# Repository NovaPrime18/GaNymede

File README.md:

# GaNymede

**Open 60 V, 100 A peak three-phase GaN motor controller, VESC compatible.**

<table><tr>
<td></td>
<td></td>
</tr></table>

---

## Overview

GaNymede is an open-source, 60 V three-phase motor controller built around six EPC2361 eGaN FETs and three LMG1210 half-bridge drivers. It is sized for a direct-drive hub motor: **50 A phase current continuously, 100 A phase peak for one minute**, with phase-current and phase-voltage sensing on every leg, Hall inputs, and an ESP32-C3 for wireless telemetry.

The board is a compact 78 × 65 mm six-layer design, with the bus capacitor bank wrapped around the power stage and the copper pours sized around the full 100 A phase peak. The control side follows the familiar VESC pattern — STM32F405, three Hall inputs, three phase-current channels.

This repository is the hardware design; it does not include firmware.

LLMs were used in the design of this driver, specifically Deepseek-V4.1-Flash(1017) was used to do schematic reviews, loss analysis, component finding.

---

## Specifications

| Parameter | Value |
|---|---|
| Bus voltage | up to 60 V DC |
| Phase current | 50 A continuous · 100 A peak (1 min) |
| Peak output power | ≈ 5.2 kW at 100 A phase peak (m = 1, modelled) |
| Topology | 3-phase inverter, 6× EPC2361 100 V eGaN |
| Switching frequency | 20 kHz nominal design point (10–40 kHz analysed) |
| Gate drive | LMG1210, 5 V, 2.2 Ω |
| Current sense | 0.25 mΩ per phase, INA240A1 |
| Control | STM32F405RGT6, 168 MHz, 8 MHz HSE |
| Wireless | ESP32-C3-WROOM-02 (Wi-Fi / BLE) |
| CAN | 2× TJA1051TK-3 (STM32 + ESP32), shared bus |
| Input | XT90 |
| Phase outputs | 3× 3 mm plated through-holes (U / V / W) |
| PCB | 78 × 65 mm, 6-layer, 1.6 mm, 1 oz Cu |

Phase currents are amplitudes, not RMS: 100 A peak is 70.7 A RMS.

---

## Hardware

| Component | Part |
|---|---|
| MCU | STM32F405RGT6 (LQFP-64) |
| Wireless | ESP32-C3-WROOM-02 |
| Power stage FETs | 6× EPC2361 (100 V eGaN) |
| Gate drivers | 3× LMG1210 |
| Current sense | 3× INA240A1, 0.25 mΩ per phase |
| Input connector | XT90 |
| Phase outputs | 3× 3 mm plated through-holes |

### Power stage

- Six EPC2361 100 V eGaN FETs, two per phase, switching a 60 V bus. The 100 V rating leaves headroom for turn-off overshoot; the real margin depends on power-loop inductance and is worth a double-pulse check.
- Each phase uses an LMG1210 driven from 5 V with 2.2 Ω gate resistors. DHL and DLH are strapped high, selecting independent high/low inputs — **dead time is set in firmware**, not by the driver.
- Bootstrap diodes are BAT46WS; each phase carries a 2.2 nF + 1 Ω snubber.
- Phase current is measured across 2× 0.5 mΩ 2512 resistors in parallel (0.25 mΩ per phase) into an INA240A1 at a gain of 20.
- The bus capacitor bank is roughly 1.4 mF (8× 100 µF 80 V, 12× 47 µF 100 V, plus ceramics), protected by an SMAJ60A TVS.
- Phase outputs land on three 3 mm plated through-holes labelled U, V and W.

---

## Thermal & loss budget

[`LOSSES.md`](LOSSES.md) contains the full copper, semiconductor and thermal model. These are **modelled** numbers, not measurements:

| | 100 A peak (1 min) | 50 A continuous |
|---|---|---|
| Total loss | ≈ 29 W | ≈ 7.3 W |
| Efficiency | ≈ 99.4 % | ≈ 99.7 % |
| Junction temperature | 45 → 62 °C | 43 °C |

Assumptions: 60 V bus, 20 kHz switching, 0.25 mΩ shunts, 0.4 mm / 6 W/mK thermal pads, 30 °C ambient — the addendum case in `LOSSES.md`.

- The **phase shunts and the 60 V / GND copper** dominate the loss budget, not the six GaNs.
- The heatsink needs to handle roughly 5–6 W continuous and up to ~20 W by the end of a 100 A minute. A 1.5–2 °C/W natural-convection sink is enough, or bolt the plate to the frame.
- The thermal pad matters more than the heatsink: a flat, thin, high-conductivity pad is worth tens of degrees at 100 A.
- The one-minute 100 A rating is limited by thermal mass, not by the heatsink.

---

## Acknowledgements / Based On

- [**VESC / bldc**](https://github.com/vedderb/bldc) — the open BLDC controller ecosystem and the control-side conventions this board follows.
- [**nitride-nano**](https://github.com/NovaPrime18/nitride-nano) — README layout, and the copper-loss analysis method reused in `LOSSES.md`.

---

## License

Hardware design files are licensed under the **CERN Open Hardware Licence Version 2 – Strongly Reciprocal (CERN-OHL-S v2.0)**.

See [`LICENSE`](./LICENSE) for the full text, or visit [ohwr.org/cern_ohl_s_v2](https://ohwr.org/cern_ohl_s_v2.txt).

> In short: you are free to use, study, modify, and distribute this design, provided that any derivatives are released under the same licence and source files are made available.

---

## Status

> 🚧 Work in progress — schematic and 6-layer layout are drawn; The current and thermal figures above are design targets from the loss model, not measured ratings.

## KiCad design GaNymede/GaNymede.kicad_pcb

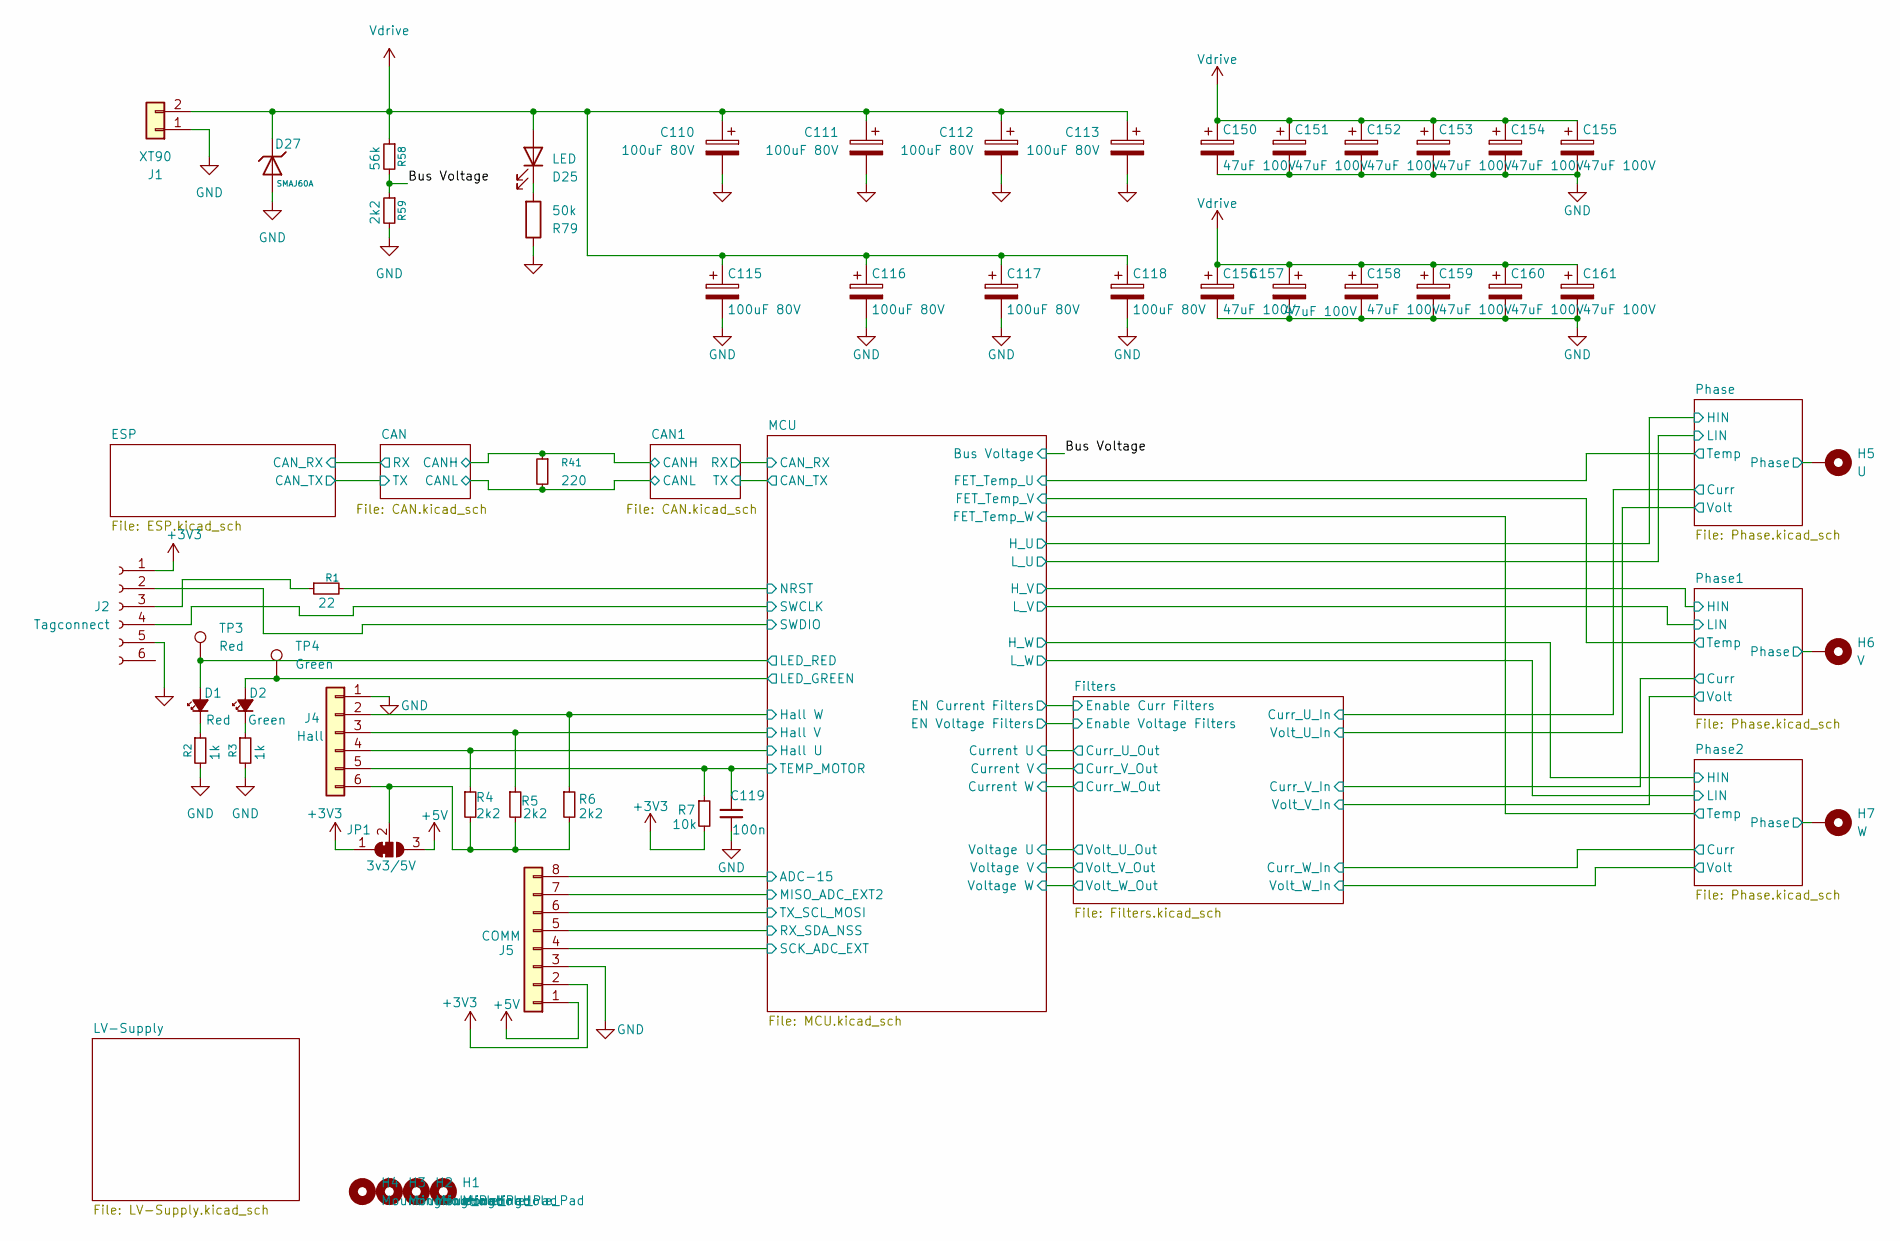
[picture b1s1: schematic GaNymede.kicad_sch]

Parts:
C110, C111, C112, C113, C115, C116, C117, C118: 100uF 80V; CP_Elec_10x10; LCSC C487410
C119: 100n; C_0402_1005Metric
C150, C151, C152, C153, C154, C155, C156, C157, C158, C159, C160, C161: 47uF 100V; CP_Elec_8x10; MPN RV100V47M8X10; LCSC C48935391
D1: Red; LED_0603_1608Metric; LCSC C2286
D2: Green; LED_0603_1608Metric; LCSC C84267
D25: LED; LED_0603_1608Metric; LCSC C2286
D27: SMAJ60A; D_SMA; Part SMAJ60A; LCSC C42394398
H1, H2, H3, H4: MountingHole_Pad; MountingHole_2.7mm_M2.5
H5: U; MountingHole_3mm_Pad_Via
H6: V; MountingHole_3mm_Pad_Via
H7: W; MountingHole_3mm_Pad_Via
J1: XT90; TH_XT90PB-M; JLC C3040688
J2: Tagconnect; Tag-Connect_TC2030-IDC-NL_2x03_P1.27mm_Vertical
J4: Hall; JST_PH_B6B-PH-SM4-TB_1x06-1MP_P2.00mm_Vertical; LCSC C471518
J5: COMM; JST_PH_B8B-PH-SM4-TB_1x08-1MP_P2.00mm_Vertical; LCSC C495548
JP1: 3v3/5V; SolderJumper-3_P1.3mm_Bridged12_RoundedPad1.0x1.5mm
R1: 22; R_0402_1005Metric; LCSC C25092
R2, R3: 1k; R_0402_1005Metric; LCSC C11702
R4, R5, R6: 2k2; R_0402_1005Metric
R7: 10k; R_0402_1005Metric
R41: 220; R_0603_1608Metric; LCSC C22962
R58: 56k; R_0603_1608Metric; LCSC C23206
R59: 2k2; R_0402_1005Metric; LCSC C25879
R79: 50k; R_0402_1005Metric; LCSC C25897
TP3: Red; TestPoint_Pad_D1.5mm
TP4: Green; TestPoint_Pad_D1.5mm

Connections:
+3V3: J2.1, J5.2, JP1.1 (A), R7.2; also elsewhere on the board
+5V: J5.1, JP1.3 (B); also elsewhere on the board
/Bus Voltage: R58.2, R59.1; also elsewhere on the board
/CAN/CANH: R41.1; also elsewhere on the board
/CAN/CANL: R41.2; also elsewhere on the board
/MCU/ADC-15: J5.8; also elsewhere on the board
/MCU/Hall U: J4.4, R4.1; also elsewhere on the board
/MCU/Hall V: J4.3, R5.1; also elsewhere on the board
/MCU/Hall W: J4.2, R6.1; also elsewhere on the board
/MCU/LED_GREEN: D2.2 (A), TP4.1 (1_1); also elsewhere on the board
/MCU/LED_RED: D1.2 (A), TP3.1 (1_1); also elsewhere on the board
/MCU/MISO_ADC_EXT2: J5.7; also elsewhere on the board
/MCU/NRST: R1.2; also elsewhere on the board
/MCU/RX_SDA_NSS: J5.5; also elsewhere on the board
/MCU/SCK_ADC_EXT: J5.4; also elsewhere on the board
/MCU/SWCLK: J2.4; also elsewhere on the board
/MCU/SWDIO: J2.2; also elsewhere on the board
/MCU/TEMP_MOTOR: C119.1, J4.5, R7.1; also elsewhere on the board
/MCU/TX_SCL_MOSI: J5.6; also elsewhere on the board
/Phase1/Phase: H6.1 (1_1); also elsewhere on the board
/Phase2/Phase: H7.1 (1_1); also elsewhere on the board
/Phase/Phase: H5.1 (1_1); also elsewhere on the board
GND: C110.2, C111.2, C112.2, C113.2, C115.2, C116.2, C117.2, C118.2, C119.2, C150.2, C151.2, C152.2, C153.2, C154.2, C155.2, C156.2, C157.2, C158.2, C159.2, C160.2, C161.2, D27.2, J1.1, J2.5, J4.1, J5.3, R2.2, R3.2, R59.2, R79.1; also elsewhere on the board
unnamed: D1.1 (K), R2.1
unnamed: D2.1 (K), R3.1
unnamed: D25.1 (K), R79.2
unnamed: J2.3, R1.1
unnamed: J4.6, JP1.2 (C), R4.2, R5.2, R6.2
Vdrive: C110.1, C111.1, C112.1, C113.1, C115.1, C116.1, C117.1, C118.1, C150.1, C151.1, C152.1, C153.1, C154.1, C155.1, C156.1, C157.1, C158.1, C159.1, C160.1, C161.1, D25.2 (A), D27.1, J1.2, R58.1; also elsewhere on the board

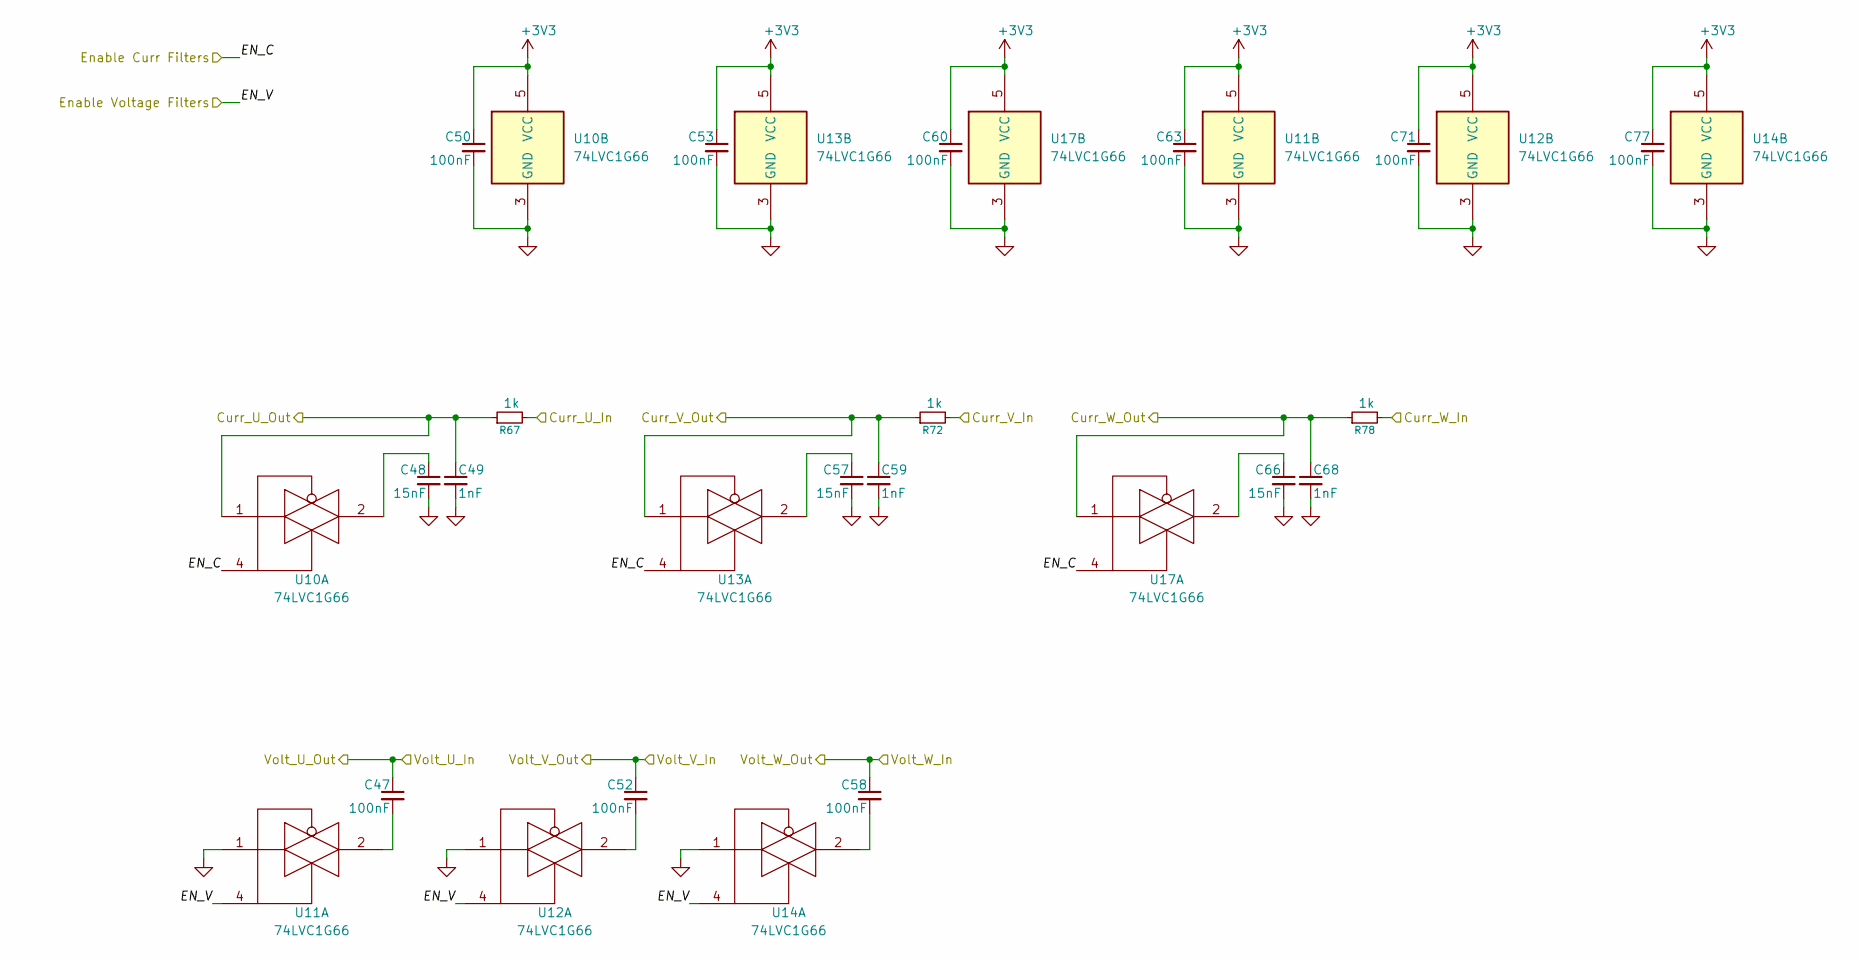
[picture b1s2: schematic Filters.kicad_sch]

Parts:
C47, C50, C52, C53, C58, C60, C63, C71, C77: 100nF; C_0402_1005Metric; LCSC C307331
C48, C57, C66: 15nF; C_0402_1005Metric; LCSC C114405
C49, C59, C68: 1nF; C_0402_1005Metric; LCSC C1523
R67, R72, R78: 1k; R_0402_1005Metric; LCSC C11702
U10, U11, U12, U13, U14, U17: 74LVC1G66; SOT-353_SC-70-5; JLC C97489

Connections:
+3V3: C50.1, C53.1, C60.1, C63.1, C71.1, C77.1, U10.5 (VCC), U11.5 (VCC), U12.5 (VCC), U13.5 (VCC), U14.5 (VCC), U17.5 (VCC); also elsewhere on the board
/Filters/Curr_U_In: R67.2; also elsewhere on the board
/Filters/Curr_U_Out: C49.1, R67.1, U10.1; also elsewhere on the board
/Filters/Curr_V_In: R72.2; also elsewhere on the board
/Filters/Curr_V_Out: C59.1, R72.1, U13.1; also elsewhere on the board
/Filters/Curr_W_In: R78.2; also elsewhere on the board
/Filters/Curr_W_Out: C68.1, R78.1, U17.1; also elsewhere on the board
/Filters/EN_C: U10.4, U13.4, U17.4; also elsewhere on the board
/Filters/EN_V: U11.4, U12.4, U14.4; also elsewhere on the board
/Filters/Volt_U_In: C47.1; also elsewhere on the board
/Filters/Volt_V_In: C52.1; also elsewhere on the board
/Filters/Volt_W_In: C58.1; also elsewhere on the board
GND: C48.2, C49.2, C50.2, C53.2, C57.2, C59.2, C60.2, C63.2, C66.2, C68.2, C71.2, C77.2, U10.3 (GND), U11.1, U11.3 (GND), U12.1, U12.3 (GND), U13.3 (GND), U14.1, U14.3 (GND), U17.3 (GND); also elsewhere on the board
unnamed: C47.2, U11.2
unnamed: C48.1, U10.2
unnamed: C52.2, U12.2
unnamed: C57.1, U13.2
unnamed: C58.2, U14.2
unnamed: C66.1, U17.2

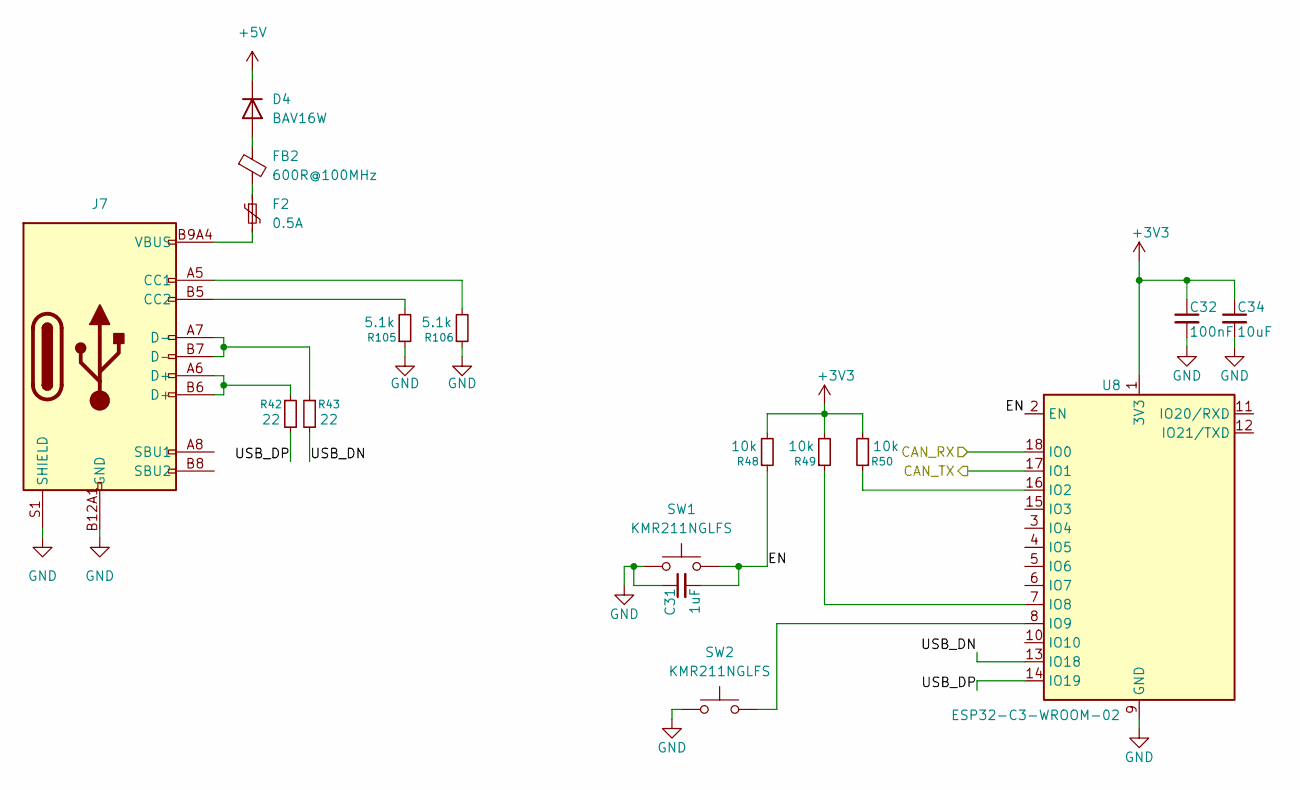
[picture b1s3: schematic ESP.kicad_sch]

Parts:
C31: 1uF; C_0402_1005Metric; LCSC C52923
C32: 100nF; C_0402_1005Metric; LCSC C307331
C34: 10uF; C_0805_2012Metric; LCSC C440198
D4: BAV16W; D_SOD-123; JLC C459527
F2: 0.5A; R_0805_2012Metric; JLC C2833485
FB2: 600R@100MHz; L_0402_1005Metric; LCSC C76884
J7: Connector, USB-TYPE-C-16P; TYPE-C-SMD_HX-TYPE-C-16PIN; LCSC C2927039
R42, R43: 22; R_0402_1005Metric; LCSC C25092
R48, R49, R50: 10k; R_0402_1005Metric; LCSC C25744
R105, R106: 5.1k; R_0402_1005Metric; LCSC C25905
SW1, SW2: KMR211NGLFS; SW_Push_1P1T_NO_CK_KMR2; JLC C221676
U8: ESP32-C3-WROOM-02; JLC C2934560

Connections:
+3V3: C32.1, C34.1, R48.2, R49.2, R50.2, U8.1 (3V3); also elsewhere on the board
+5V: D4.1 (K); also elsewhere on the board
/CAN/RX: U8.18 (IO0); also elsewhere on the board
/CAN/TX: U8.17 (IO1); also elsewhere on the board
/ESP/EN: C31.2, R48.1, SW1.2, U8.2 (EN)
/ESP/USB_DN: R43.2, U8.13 (IO18)
/ESP/USB_DP: R42.2, U8.14 (IO19)
GND: C31.1, C32.2, C34.2, J7.A12B1 (GND), J7.B12A1 (GND), J7.S1 (SHIELD), R105.1, R106.1, SW1.1, SW2.1, U8.9 (GND), U8.19 (GND); also elsewhere on the board
unnamed: D4.2 (A), FB2.1
unnamed: F2.1, FB2.2
unnamed: F2.2, J7.A9B4 (VBUS), J7.B9A4 (VBUS)
unnamed: J7.A5 (CC1), R106.2
unnamed: J7.B5 (CC2), R105.2
unnamed: J7.A6 (D+), J7.B6 (D+), R42.1
unnamed: J7.A7 (D-), J7.B7 (D-), R43.1
unnamed: R50.1, U8.16 (IO2)
unnamed: R49.1, U8.7 (IO8)
unnamed: SW2.2, U8.8 (IO9)

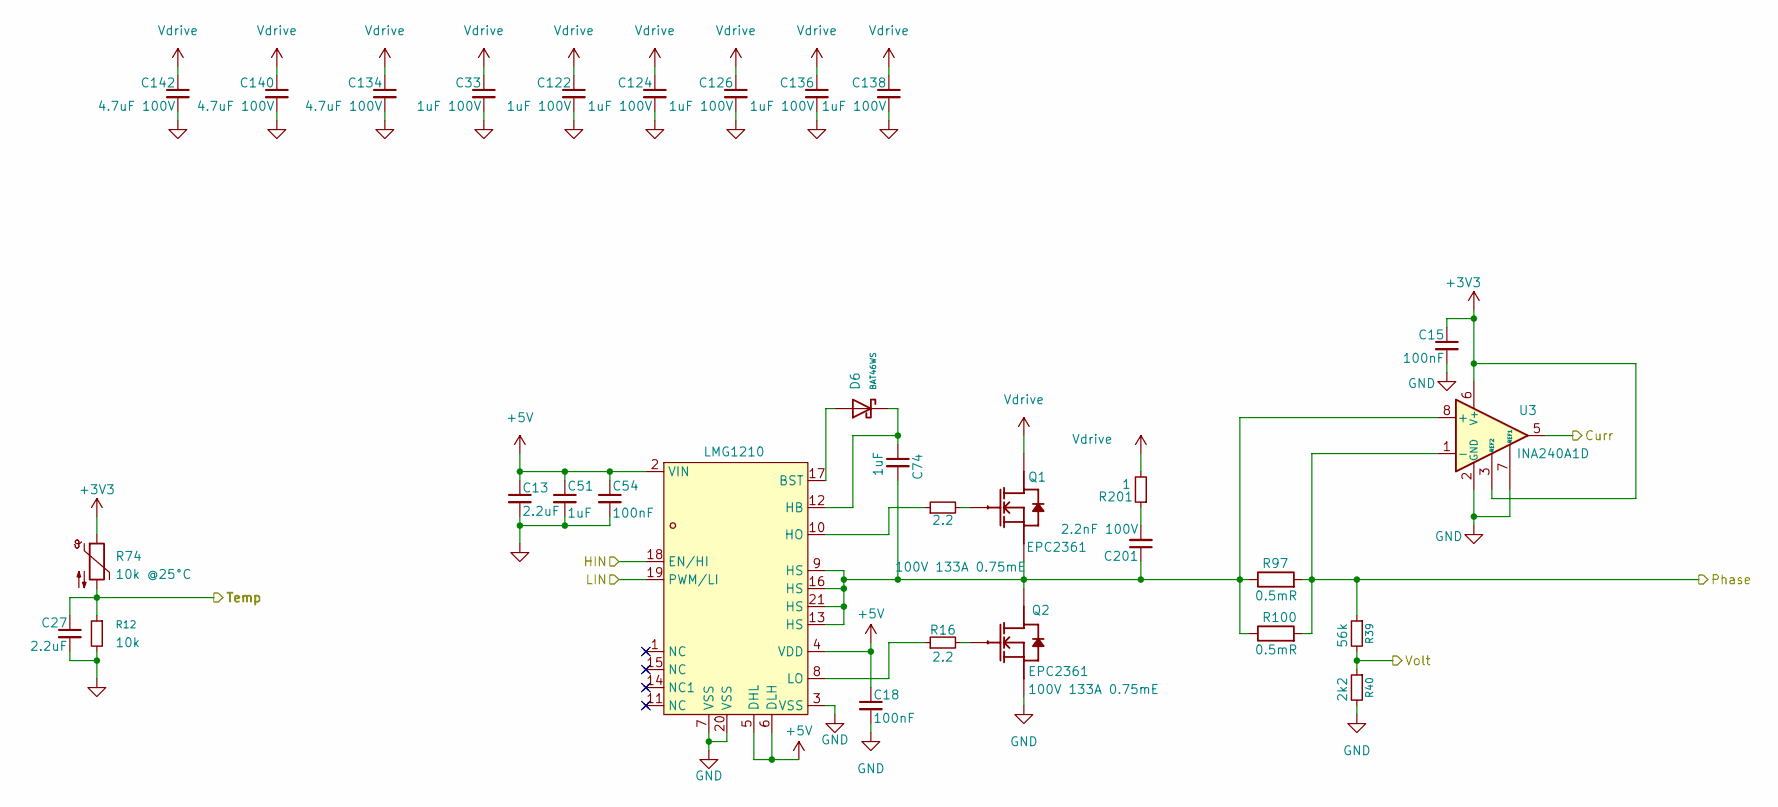
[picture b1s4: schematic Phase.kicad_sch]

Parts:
C13, C27: 2.2uF; C_0402_1005Metric; LCSC C20539421
C15, C18: 100nF; C_0402_1005Metric; LCSC C307331
C33, C122, C124, C126, C136, C138: 1uF 100V; C_0805_2012Metric; LCSC C5370002
C51, C74: 1uF; C_0402_1005Metric
C54: 100nF; C_0402_1005Metric
C134, C140, C142: 4.7uF 100V; C_1206_3216Metric; LCSC C22367839
C201: 2.2nF 100V; C_0805_2012Metric; MPN CC0805KRX7R0BB222; LCSC C107136
D6: BAT46WS; D_SOD-323; Forward Voltage (Vf@If) 1V@250mA; Reverse Voltage (Vr) 100V; Part BAT46WS; LCSC C7502692
Q1, Q2: EPC2361; D0606F_100V
R12: 10k; R_0402_1005Metric; LCSC C25744
R13, R16: 2.2; R_0402_1005Metric
R39: 56k; R_0603_1608Metric; LCSC C23206
R40: 2k2; R_0402_1005Metric; LCSC C25879
R74: 10k @25°C; R_0402_1005Metric; LCSC C77131
R97, R100: 0.5mR; R_2512_6332Metric
R201: 1; R_1210_3225Metric; MPN FRC1210J1R0 TS; LCSC C2974068
U3: INA240A1D; SOIC-8_3.9x4.9mm_P1.27mm; LCSC C1346458
U19: LMG1210; WQFN-19_L4.0-W3.0-P0.50-BL-EP_LMG1210RVRR; MPN LMG1210RVRR; LCSC Part C2677136

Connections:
+3V3: C15.1, R74.1, U3.3 (REF2), U3.6 (V+); also elsewhere on the board
+5V: C13.1, C18.1, C51.1, C54.1, U19.2 (VIN), U19.4 (VDD), U19.5 (DHL), U19.6 (DLH); also elsewhere on the board
/Filters/Curr_U_In: U3.5; also elsewhere on the board
/Filters/Volt_U_In: R39.2, R40.1; also elsewhere on the board
/MCU/FET_Temp_U: C27.1, R12.1, R74.2; also elsewhere on the board
/MCU/H_U: U19.18 (EN/HI); also elsewhere on the board
/MCU/L_U: U19.19 (PWM/LI); also elsewhere on the board
/Phase/Phase: R39.1, R97.2, R100.2, U3.1 (-); also elsewhere on the board
GND: C13.2, C15.2, C18.2, C27.2, C33.2, C51.2, C54.2, C122.2, C124.2, C126.2, C134.2, C136.2, C138.2, C140.2, C142.2, Q2.2 (S), Q2.4 (S), Q2.6 (S), R12.2, R40.2, U3.2 (GND), U3.4 (GND), U3.7 (REF1), U19.3 (VSS), U19.7 (VSS), U19.20 (VSS); also elsewhere on the board
unnamed: C201.2, R201.1
unnamed: Q1.1 (G), R13.2
unnamed: Q2.1 (G), R16.2
unnamed: C74.2, C201.1, Q1.2 (S), Q1.4 (S), Q1.6 (S), Q2.3 (D), Q2.5 (D), Q2.7 (D), R97.1, R100.1, U3.8 (+), U19.9 (HS), U19.13 (HS), U19.16 (HS), U19.21 (HS)
unnamed: D6.2, U19.17 (BST)
unnamed: C74.1, D6.1, U19.12 (HB)
unnamed: R13.1, U19.10 (HO)
unnamed: R16.1, U19.8 (LO)
Vdrive: C33.1, C122.1, C124.1, C126.1, C134.1, C136.1, C138.1, C140.1, C142.1, Q1.3 (D), Q1.5 (D), Q1.7 (D), R201.2; also elsewhere on the board

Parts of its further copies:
C14, C17, C28, C39: 2.2uF; C_0402_1005Metric; LCSC C20539421
C16, C19, C20, C21: 100nF; C_0402_1005Metric; LCSC C307331
C35, C38, C123, C125, C127, C128, C129, C130, C137, C139, C147, C148: 1uF 100V; C_0805_2012Metric; LCSC C5370002
C64, C70, C75, C76: 1uF; C_0402_1005Metric
C67, C73: 100nF; C_0402_1005Metric
C135, C141, C143, C144, C145, C146: 4.7uF 100V; C_1206_3216Metric; LCSC C22367839
C202, C203: 2.2nF 100V; C_0805_2012Metric; MPN CC0805KRX7R0BB222; LCSC C107136
D7, D8: BAT46WS; D_SOD-323; Forward Voltage (Vf@If) 1V@250mA; Reverse Voltage (Vr) 100V; Part BAT46WS; LCSC C7502692
Q3, Q4, Q5, Q6: EPC2361; D0606F_100V
R14, R18: 10k; R_0402_1005Metric; LCSC C25744
R15, R17, R19, R20: 2.2; R_0402_1005Metric
R46, R51: 56k; R_0603_1608Metric; LCSC C23206
R47, R52: 2k2; R_0402_1005Metric; LCSC C25879
R75, R76: 10k @25°C; R_0402_1005Metric; LCSC C77131
R98, R99, R101, R102: 0.5mR; R_2512_6332Metric
R202, R203: 1; R_1210_3225Metric; MPN FRC1210J1R0 TS; LCSC C2974068
U4, U5: INA240A1D; SOIC-8_3.9x4.9mm_P1.27mm; LCSC C1346458
U20, U21: LMG1210; WQFN-19_L4.0-W3.0-P0.50-BL-EP_LMG1210RVRR; MPN LMG1210RVRR; LCSC Part C2677136

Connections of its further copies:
+3V3: C16.1, C21.1, R75.1, R76.1, U4.3 (REF2), U4.6 (V+), U5.3 (REF2), U5.6 (V+); also elsewhere on the board
+5V: C14.1, C17.1, C19.1, C20.1, C64.1, C67.1, C70.1, C73.1, U20.2 (VIN), U20.4 (VDD), U20.5 (DHL), U20.6 (DLH), U21.2 (VIN), U21.4 (VDD), U21.5 (DHL), U21.6 (DLH); also elsewhere on the board
/Filters/Curr_V_In: U4.5; also elsewhere on the board
/Filters/Curr_W_In: U5.5; also elsewhere on the board
/Filters/Volt_V_In: R46.2, R47.1; also elsewhere on the board
/Filters/Volt_W_In: R51.2, R52.1; also elsewhere on the board
/MCU/FET_Temp_V: C28.1, R14.1, R75.2; also elsewhere on the board
/MCU/FET_Temp_W: C39.1, R18.1, R76.2; also elsewhere on the board
/MCU/H_V: U20.18 (EN/HI); also elsewhere on the board
/MCU/H_W: U21.18 (EN/HI); also elsewhere on the board
/MCU/L_V: U20.19 (PWM/LI); also elsewhere on the board
/MCU/L_W: U21.19 (PWM/LI); also elsewhere on the board
/Phase1/Phase: R46.1, R98.2, R101.2, U4.1 (-); also elsewhere on the board
/Phase2/Phase: R51.1, R99.2, R102.2, U5.1 (-); also elsewhere on the board
GND: C14.2, C16.2, C17.2, C19.2, C20.2, C21.2, C28.2, C35.2, C38.2, C39.2, C64.2, C67.2, C70.2, C73.2, C123.2, C125.2, C127.2, C128.2, C129.2, C130.2, C135.2, C137.2, C139.2, C141.2, C143.2, C144.2, C145.2, C146.2, C147.2, C148.2, Q4.2 (S), Q4.4 (S), Q4.6 (S), Q6.2 (S), Q6.4 (S), Q6.6 (S), R14.2, R18.2, R47.2, R52.2, U4.2 (GND), U4.4 (GND), U4.7 (REF1), U5.2 (GND), U5.4 (GND), U5.7 (REF1), U20.3 (VSS), U20.7 (VSS), U20.20 (VSS), U21.3 (VSS), U21.7 (VSS), U21.20 (VSS); also elsewhere on the board
unnamed: C202.2, R202.1
unnamed: C203.2, R203.1
unnamed: Q3.1 (G), R15.2
unnamed: Q4.1 (G), R17.2
unnamed: Q5.1 (G), R20.2
unnamed: Q6.1 (G), R19.2
unnamed: C75.2, C202.1, Q3.2 (S), Q3.4 (S), Q3.6 (S), Q4.3 (D), Q4.5 (D), Q4.7 (D), R98.1, R101.1, U4.8 (+), U20.9 (HS), U20.13 (HS), U20.16 (HS), U20.21 (HS)
unnamed: C76.2, C203.1, Q5.2 (S), Q5.4 (S), Q5.6 (S), Q6.3 (D), Q6.5 (D), Q6.7 (D), R99.1, R102.1, U5.8 (+), U21.9 (HS), U21.13 (HS), U21.16 (HS), U21.21 (HS)
unnamed: D7.2, U20.17 (BST)
unnamed: C75.1, D7.1, U20.12 (HB)
unnamed: R15.1, U20.10 (HO)
unnamed: R17.1, U20.8 (LO)
unnamed: D8.2, U21.17 (BST)
unnamed: C76.1, D8.1, U21.12 (HB)
unnamed: R20.1, U21.10 (HO)
unnamed: R19.1, U21.8 (LO)
Vdrive: C35.1, C38.1, C123.1, C125.1, C127.1, C128.1, C129.1, C130.1, C135.1, C137.1, C139.1, C141.1, C143.1, C144.1, C145.1, C146.1, C147.1, C148.1, Q3.3 (D), Q3.5 (D), Q3.7 (D), Q5.3 (D), Q5.5 (D), Q5.7 (D), R202.2, R203.2; also elsewhere on the board

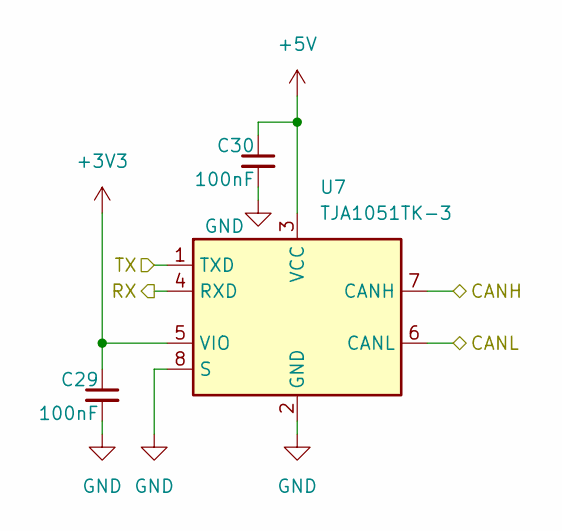
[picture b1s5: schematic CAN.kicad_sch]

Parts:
C29, C30: 100nF; C_0402_1005Metric; LCSC C307331
U7: TJA1051TK-3; HVSON-8-1EP_3x3mm_P0.65mm_EP1.6x2.4mm; JLC C2875699

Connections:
+3V3: C29.1, U7.5 (VIO); also elsewhere on the board
+5V: C30.1, U7.3 (VCC); also elsewhere on the board
/CAN/CANH: U7.7 (CANH); also elsewhere on the board
/CAN/CANL: U7.6 (CANL); also elsewhere on the board
/CAN/RX: U7.4 (RXD); also elsewhere on the board
/CAN/TX: U7.1 (TXD); also elsewhere on the board
GND: C29.2, C30.2, U7.2 (GND), U7.8 (S), U7.9 (GND); also elsewhere on the board

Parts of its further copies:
C36, C37: 100nF; C_0402_1005Metric; LCSC C307331
U18: TJA1051TK-3; HVSON-8-1EP_3x3mm_P0.65mm_EP1.6x2.4mm; JLC C2875699

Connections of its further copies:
+3V3: C36.1, U18.5 (VIO); also elsewhere on the board
+5V: C37.1, U18.3 (VCC); also elsewhere on the board
/CAN1/RX: U18.4 (RXD); also elsewhere on the board
/CAN1/TX: U18.1 (TXD); also elsewhere on the board
/CAN/CANH: U18.7 (CANH); also elsewhere on the board
/CAN/CANL: U18.6 (CANL); also elsewhere on the board
GND: C36.2, C37.2, U18.2 (GND), U18.8 (S), U18.9 (GND); also elsewhere on the board

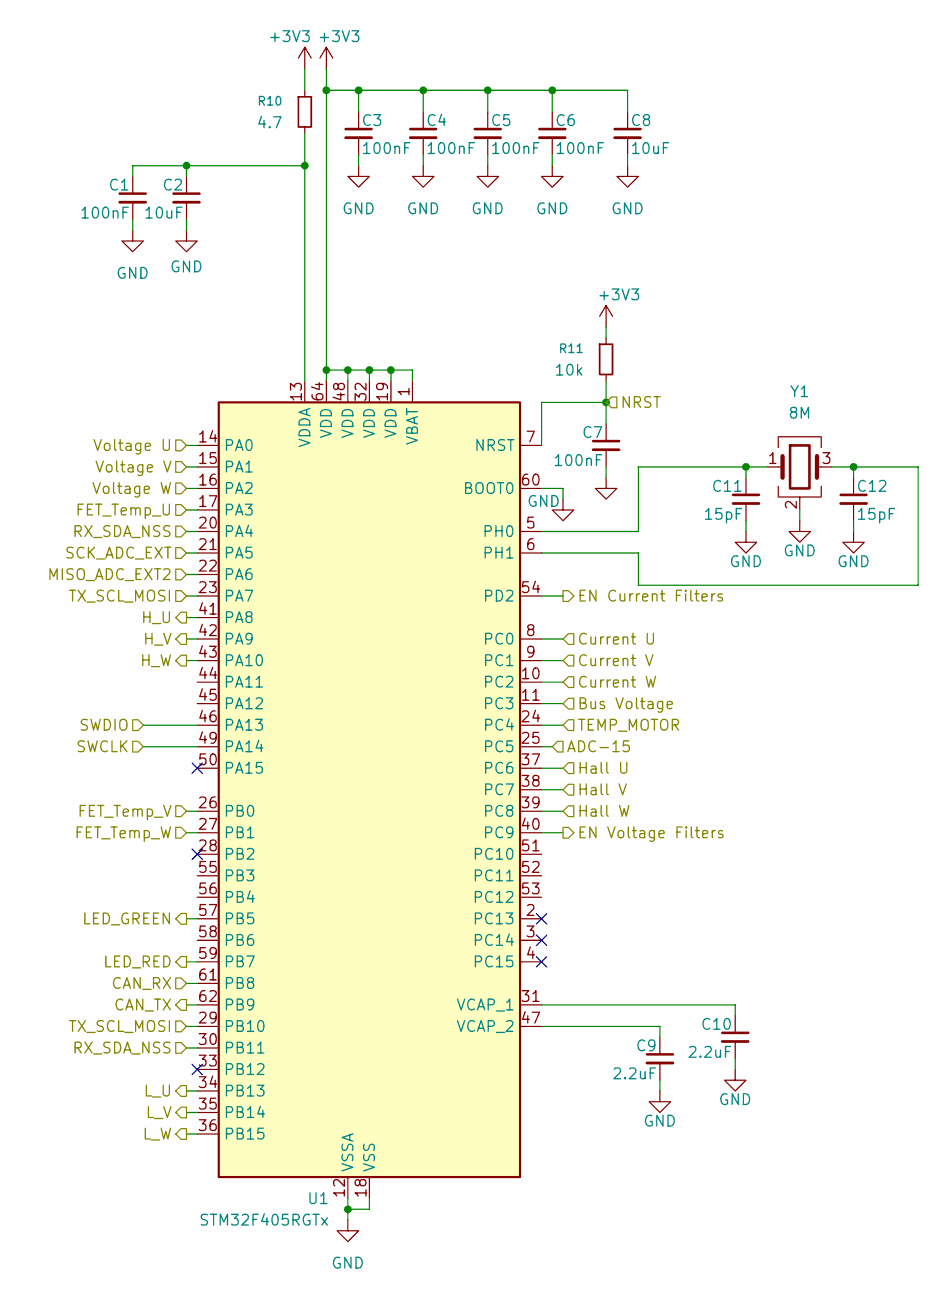
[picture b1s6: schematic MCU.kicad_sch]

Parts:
C1, C3, C4, C5, C6, C7: 100nF; C_0402_1005Metric; LCSC C307331
C2, C8: 10uF; C_0805_2012Metric; LCSC C440198
C9, C10: 2.2uF; C_0402_1005Metric; LCSC C20539421
C11, C12: 15pF; C_0402_1005Metric; LCSC C1548
R10: 4.7; R_0402_1005Metric; LCSC C25121
R11: 10k; R_0402_1005Metric; LCSC C25744
U1: STM32F405RGTx; LQFP-64_10x10mm_P0.5mm; LCSC C15742
Y1: 8M; Crystal_SMD_3225-4Pin_3.2x2.5mm; JLC C2682775

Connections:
+3V3: C3.1, C4.1, C5.1, C6.1, C8.1, R10.1, R11.1, U1.1 (VBAT), U1.19 (VDD), U1.32 (VDD), U1.48 (VDD), U1.64 (VDD); also elsewhere on the board
/Bus Voltage: U1.11 (PC3); also elsewhere on the board
/CAN1/RX: U1.61 (PB8); also elsewhere on the board
/CAN1/TX: U1.62 (PB9); also elsewhere on the board
/Filters/Curr_U_Out: U1.8 (PC0); also elsewhere on the board
/Filters/Curr_V_Out: U1.9 (PC1); also elsewhere on the board
/Filters/Curr_W_Out: U1.10 (PC2); also elsewhere on the board
/Filters/EN_C: U1.54 (PD2); also elsewhere on the board
/Filters/EN_V: U1.40 (PC9); also elsewhere on the board
/Filters/Volt_U_In: U1.14 (PA0); also elsewhere on the board
/Filters/Volt_V_In: U1.15 (PA1); also elsewhere on the board
/Filters/Volt_W_In: U1.16 (PA2); also elsewhere on the board
/MCU/ADC-15: U1.25 (PC5); also elsewhere on the board
/MCU/FET_Temp_U: U1.17 (PA3); also elsewhere on the board
/MCU/FET_Temp_V: U1.26 (PB0); also elsewhere on the board
/MCU/FET_Temp_W: U1.27 (PB1); also elsewhere on the board
/MCU/H_U: U1.41 (PA8); also elsewhere on the board
/MCU/H_V: U1.42 (PA9); also elsewhere on the board
/MCU/H_W: U1.43 (PA10); also elsewhere on the board
/MCU/Hall U: U1.37 (PC6); also elsewhere on the board
/MCU/Hall V: U1.38 (PC7); also elsewhere on the board
/MCU/Hall W: U1.39 (PC8); also elsewhere on the board
/MCU/LED_GREEN: U1.57 (PB5); also elsewhere on the board
/MCU/LED_RED: U1.59 (PB7); also elsewhere on the board
/MCU/L_U: U1.34 (PB13); also elsewhere on the board
/MCU/L_V: U1.35 (PB14); also elsewhere on the board
/MCU/L_W: U1.36 (PB15); also elsewhere on the board
/MCU/MISO_ADC_EXT2: U1.22 (PA6); also elsewhere on the board
/MCU/NRST: C7.1, R11.2, U1.7 (NRST); also elsewhere on the board
/MCU/RX_SDA_NSS: U1.20 (PA4), U1.30 (PB11); also elsewhere on the board
/MCU/SCK_ADC_EXT: U1.21 (PA5); also elsewhere on the board
/MCU/SWCLK: U1.49 (PA14); also elsewhere on the board
/MCU/SWDIO: U1.46 (PA13); also elsewhere on the board
/MCU/TEMP_MOTOR: U1.24 (PC4); also elsewhere on the board
/MCU/TX_SCL_MOSI: U1.23 (PA7), U1.29 (PB10); also elsewhere on the board
GND: C1.2, C2.2, C3.2, C4.2, C5.2, C6.2, C7.2, C8.2, C9.2, C10.2, C11.2, C12.2, U1.12 (VSSA), U1.18 (VSS), U1.60 (BOOT0), U1.63 (VSS), Y1.2 (G), Y1.4 (G); also elsewhere on the board
unnamed: C11.1, U1.5 (PH0), Y1.1
unnamed: C12.1, U1.6 (PH1), Y1.3
unnamed: C10.1, U1.31 (VCAP_1)
unnamed: C9.1, U1.47 (VCAP_2)
unnamed: C1.1, C2.1, R10.2, U1.13 (VDDA)

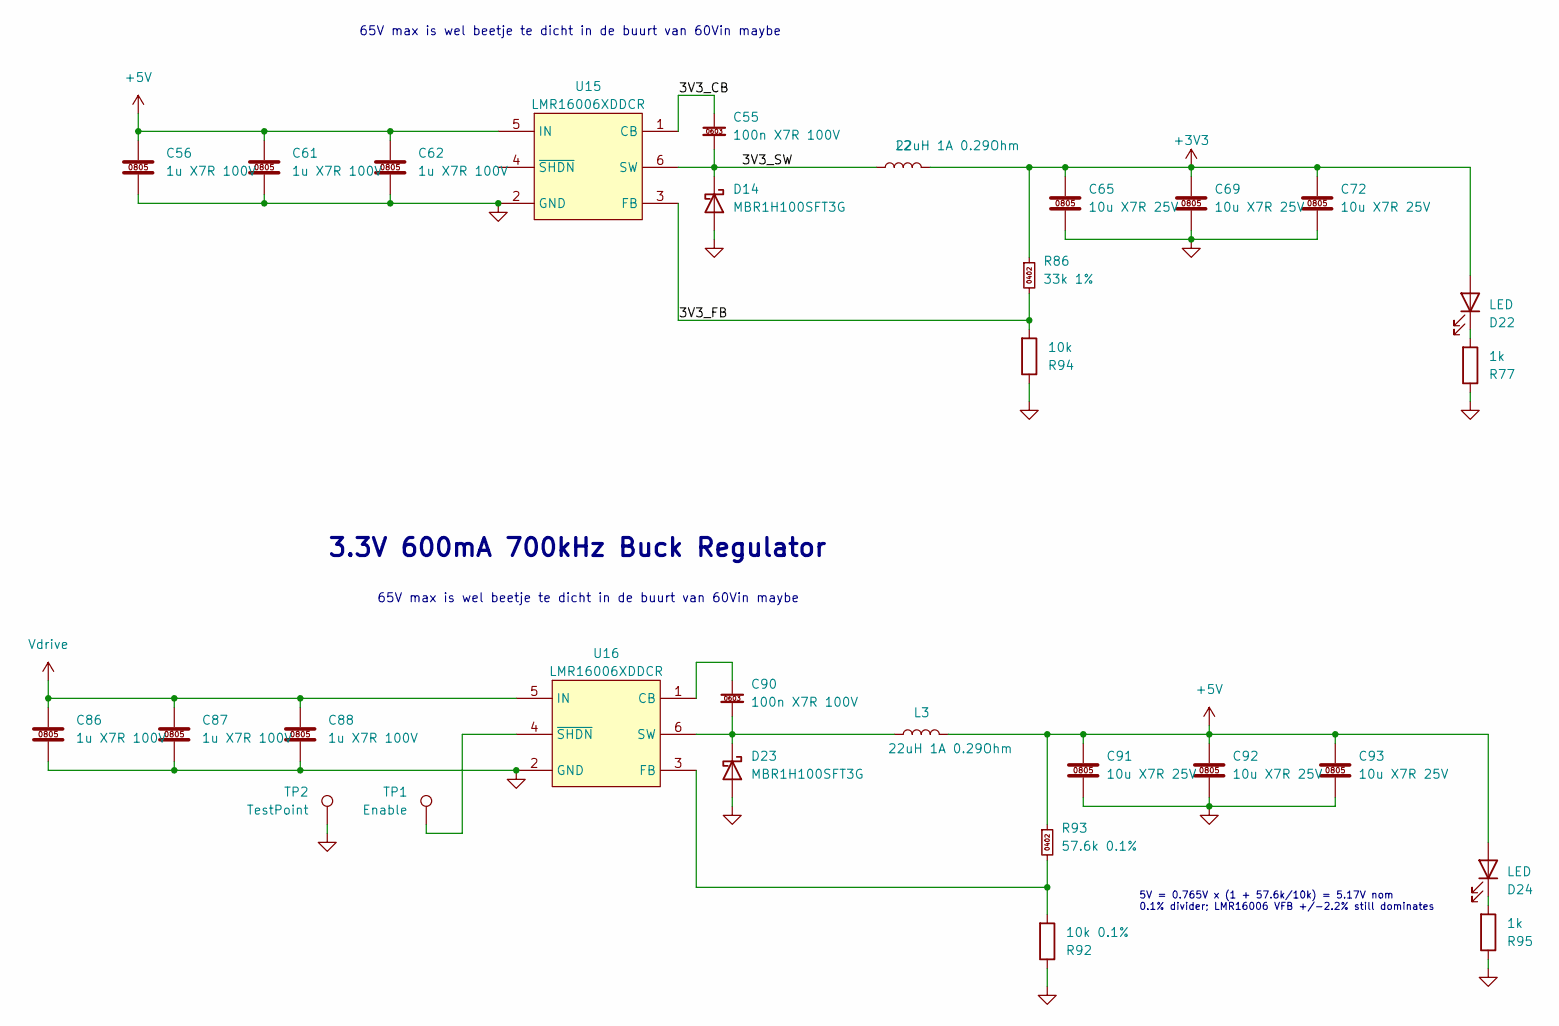
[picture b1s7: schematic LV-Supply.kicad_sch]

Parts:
C55, C90: 100n X7R 100V; C_0603_1608Metric; Manufacturer Part Number CL10B104KC8NNNC; LCSC C15725
C56, C61, C62, C86, C87, C88: 1u X7R 100V; C_0805_2012Metric; Manufacturer Part Number CC0805KKX7R0BB105; LCSC C5370002
C65, C69, C72, C91, C92, C93: 10u X7R 25V; C_0805_2012Metric; Manufacturer Part Number CL21B106KAYQNNE; LCSC C3039694
D14, D23: MBR1H100SFT3G; D_SOD-123F; Manufacturer Part Number MBR1H100SFT3G; LCSC C235757
D22, D24: LED; LED_0603_1608Metric; LCSC C2286
L2, L3: 22uH 1A 0.29Ohm; L_Sunlord_SWPA4030S; Manufacturer Part Number SWPA4030S220MT; LCSC C167883
R77, R95: 1k; R_0402_1005Metric; LCSC C106235
R86: 33k 1%; R_0402_1005Metric; Manufacturer Part Number RC0402FR-0733KL; LCSC C138003
R92: 10k 0.1%; R_0402_1005Metric; Tolerance ±0.1%; Manufacturer Part Number RT0402BRD0710KL; LCSC C190095
R93: 57.6k 0.1%; R_0402_1005Metric; Tolerance ±0.1%; Manufacturer Part Number RT0402BRD0757K6L; LCSC C852849
R94: 10k; R_0402_1005Metric; LCSC C2906861
TP1: Enable; TestPoint_Pad_D1.5mm
TP2: TestPoint; TestPoint_Pad_D1.5mm
U15, U16: LMR16006XDDCR; SOT-23-6; Manufacturer Part Number LMR16006XDDCR; LCSC C87080

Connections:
+3V3: C65.1, C69.1, C72.1, D22.2 (A), L2.2, R86.1; also elsewhere on the board
+5V: C56.1, C61.1, C62.1, C91.1, C92.1, C93.1, D24.2 (A), L3.2, R93.1, U15.5 (IN); also elsewhere on the board
/LV-Supply/3V3_CB: C55.1, U15.1 (CB)
/LV-Supply/3V3_FB: R86.2, R94.2, U15.3 (FB)
/LV-Supply/3V3_SW: C55.2, D14.1 (K), L2.1, U15.6 (SW)
GND: C56.2, C61.2, C62.2, C65.2, C69.2, C72.2, C86.2, C87.2, C88.2, C91.2, C92.2, C93.2, D14.2 (A), D23.2 (A), R77.1, R92.1, R94.1, R95.1, TP2.1 (1_1), U15.2 (GND), U16.2 (GND); also elsewhere on the board
unnamed: D22.1 (K), R77.2
unnamed: C90.2, D23.1 (K), L3.1, U16.6 (SW)
unnamed: D24.1 (K), R95.2
unnamed: C90.1, U16.1 (CB)
unnamed: R92.2, R93.2, U16.3 (FB)
unnamed: TP1.1 (1_1), U16.4 (~SHDN)
Vdrive: C86.1, C87.1, C88.1, U16.5 (IN); also elsewhere on the board

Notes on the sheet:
5V = 0.765V x (1 + 57.6k/10k) = 5.17V nom 0.1% divider; LMR16006 VFB +/-2.2% still dominates
65V max is wel beetje te dicht in de buurt van 60Vin maybe
3.3V 600mA 700kHz Buck Regulator

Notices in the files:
README.md:
License: CERN-OHL-S v2.0
